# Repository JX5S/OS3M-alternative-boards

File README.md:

# OS3M-alternative-boards
Boards based on the OS3M project, using 0603s and other components I like. I tried to get as few KiCAD warning as possible.

I haven't tested the boards and I'm planning to change them further before ordering, this repository is just for reference.

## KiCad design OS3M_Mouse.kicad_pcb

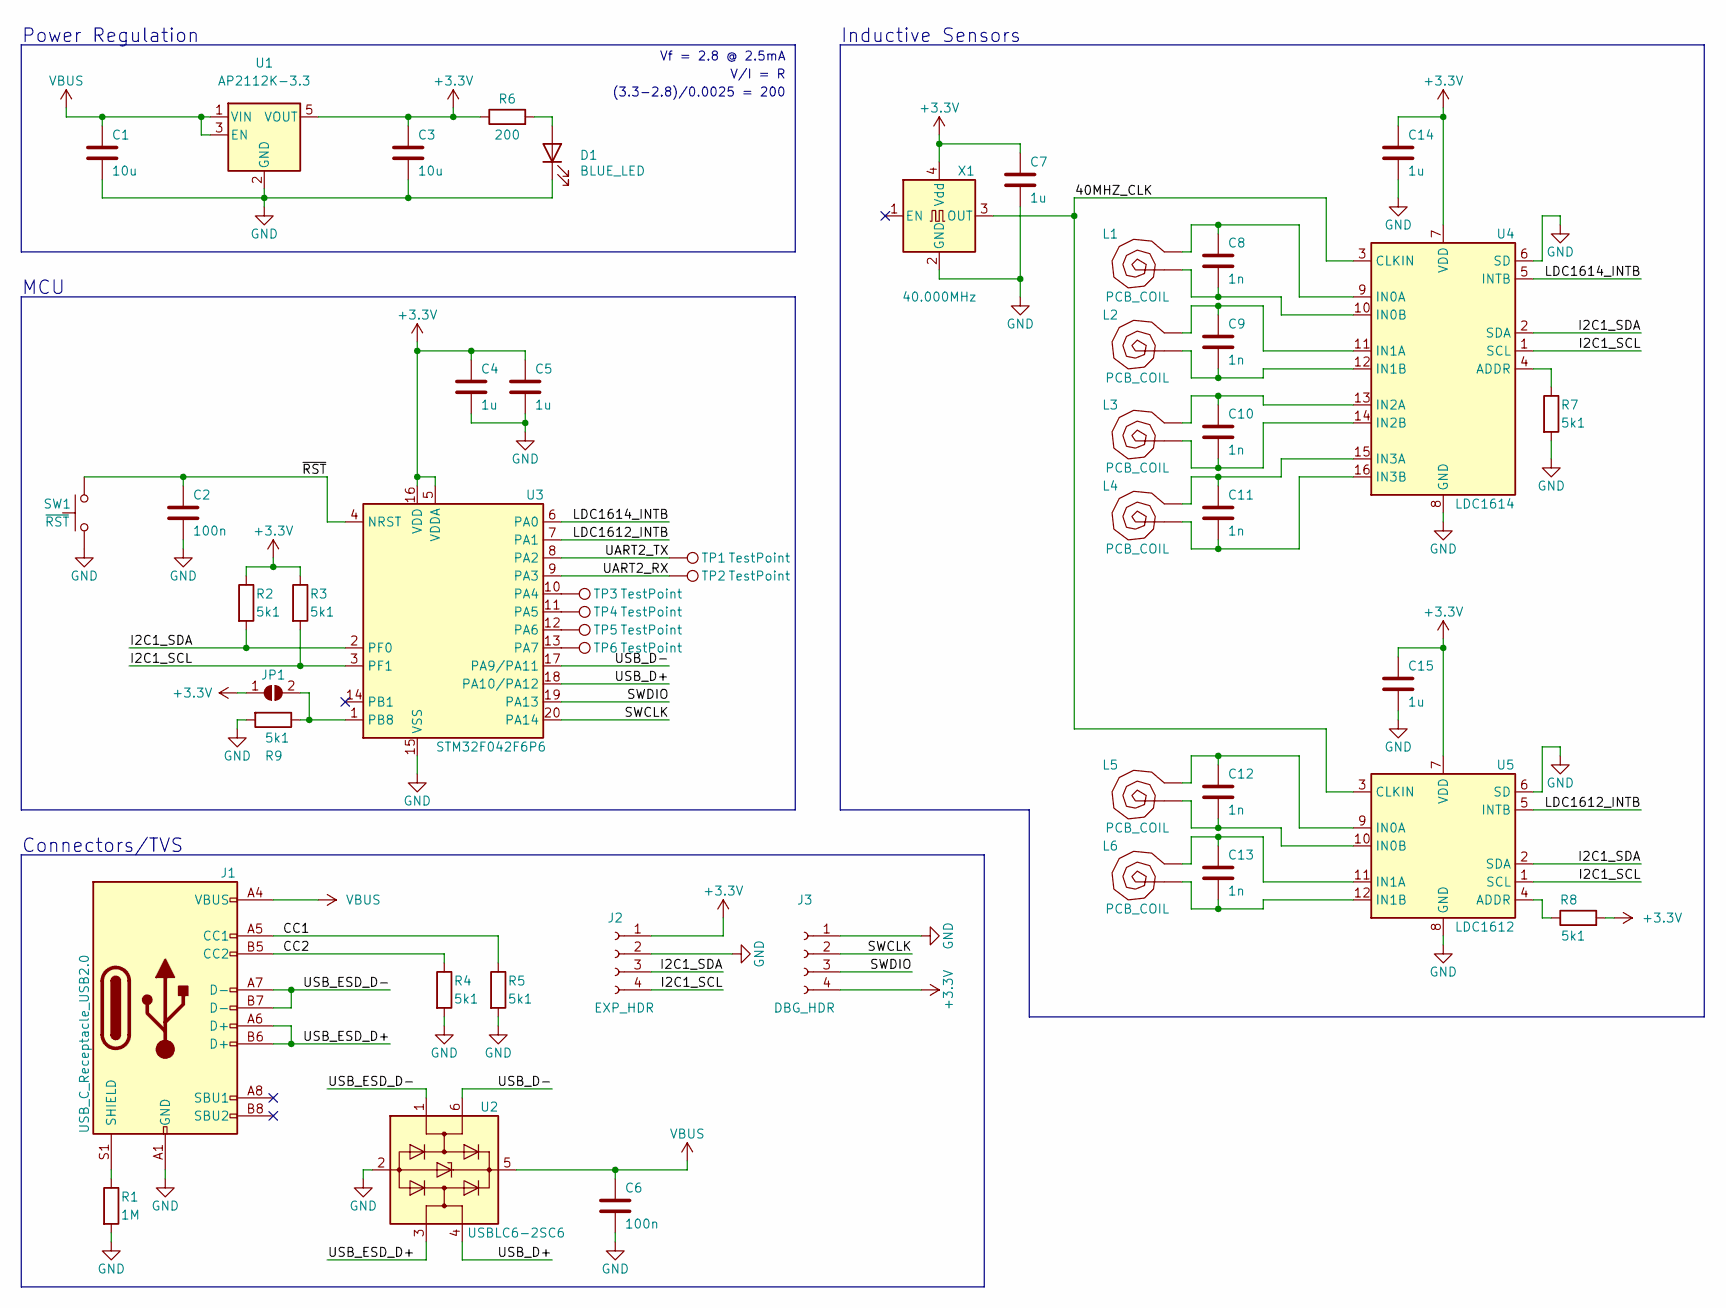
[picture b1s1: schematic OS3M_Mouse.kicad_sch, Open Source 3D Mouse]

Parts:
C1, C3: 10u; C_0603_1608Metric; LCSC C19702
C2, C6: 100n; C_0603_1608Metric; LCSC C14663
C4, C5, C7, C14, C15: 1u; C_0603_1608Metric; LCSC C15849
C8, C9, C10, C11, C12, C13: 1n; C_0603_1608Metric; LCSC C1588
D1: BLUE_LED; LED_0603_1608Metric; LCSC C72043
J1: USB_C_Receptacle_USB2.0; USB_C_Receptacle_G-Switch_GT-USB-7010ASV; LCSC C2988369
J2: EXP_HDR; PinSocket_2x02_P2.54mm_Horizontal
J3: DBG_HDR; PinHeader_1x04_P2.54mm_Vertical
JP1: SolderJumper_2_Open; SolderJumper-2_P1.3mm_Open_RoundedPad1.0x1.5mm
L1, L2, L3, L4, L5, L6: PCB_COIL; COIL_GENERATOR_0
R1: 1M; R_0603_1608Metric; LCSC C22935
R2, R3, R4, R5, R7, R8, R9: 5k1; R_0603_1608Metric; LCSC C23186
R6: 200; R_0603_1608Metric; LCSC C8218
SW1: ~{RST}; SW_Push_1P1T_XKB_TS-1187A; LCSC C318884
TP1, TP2, TP3, TP4, TP5, TP6: TestPoint; TestPoint_Pad_D2.0mm
U1: AP2112K-3.3; SOT-23-5; LCSC C51118
U2: USBLC6-2SC6; SOT-23-6; LCSC C2827654
U3: STM32F042F6P6; TSSOP-20_4.4x6.5mm_P0.65mm; LCSC C2969989
U4: LDC1614; WQFN-16-1EP_4x4mm_P0.5mm_EP2.6x2.6mm_ThermalVias; LCSC C968448
U5: LDC1612; WSON-12-1EP_4x4mm_P0.5mm_EP2.6x3mm_ThermalVias; LCSC C202191
X1: 40.000MHz; Crystal_SMD_3225-4Pin_3.2x2.5mm; LCSC C387435

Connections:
+3.3V: C3.1, C4.1, C5.1, C7.1, C14.1, C15.1, J2.1, J3.4, JP1.1 (A), R2.1, R3.1, R6.1, R8.2, U1.5 (VOUT), U3.5 (VDDA), U3.16 (VDD), U4.7 (VDD), U5.7 (VDD), X1.4 (Vdd)
/40MHZ_CLK: U4.3 (CLKIN), U5.3 (CLKIN), X1.3 (OUT)
/CC1: J1.A5 (CC1), R5.1
/CC2: J1.B5 (CC2), R4.1
/I2C1_SCL: J2.4, R3.2, U3.3 (PF1), U4.1 (SCL), U5.1 (SCL)
/I2C1_SDA: J2.3, R2.2, U3.2 (PF0), U4.2 (SDA), U5.2 (SDA)
/LDC1612_INTB: U3.7 (PA1), U5.5 (INTB)
/LDC1614_INTB: U3.6 (PA0), U4.5 (INTB)
/SWCLK: J3.2, U3.20 (PA14)
/SWDIO: J3.3, U3.19 (PA13)
/UART2_RX: TP2.1, U3.9 (PA3)
/UART2_TX: TP1.1, U3.8 (PA2)
/USB_D+: U2.4 (I/O2), U3.18 (PA10/PA12)
/USB_D-: U2.6 (I/O1), U3.17 (PA9/PA11)
/USB_ESD_D+: J1.A6 (D+), J1.B6 (D+), U2.3 (I/O2)
/USB_ESD_D-: J1.A7 (D-), J1.B7 (D-), U2.1 (I/O1)
/~RST: C2.1, SW1.2, U3.4 (NRST)
GND: C1.2, C2.2, C3.2, C4.2, C5.2, C6.2, C7.2, C14.2, C15.2, D1.1 (K), J1.A1 (GND), J1.A12 (GND), J1.B1 (GND), J1.B12 (GND), J2.2, J3.1, R1.2, R4.2, R5.2, R7.2, R9.2, SW1.1, U1.2 (GND), U2.2 (GND), U3.15 (VSS), U4.6 (SD), U4.8 (GND), U4.17 (GND), U5.6 (SD), U5.8 (GND), U5.13 (GND), X1.2 (GND)
unnamed: D1.2 (A), R6.2
unnamed: J1.S1 (SHIELD), R1.1
unnamed: JP1.2 (B), R9.1, U3.1 (PB8)
unnamed: TP3.1, U3.10 (PA4)
unnamed: TP4.1, U3.11 (PA5)
unnamed: TP5.1, U3.12 (PA6)
unnamed: TP6.1, U3.13 (PA7)
unnamed: R7.1, U4.4 (ADDR)
unnamed: C8.1, L1.1, U4.9 (IN0A)
unnamed: C8.2, L1.2, U4.10 (IN0B)
unnamed: C9.1, L2.1, U4.11 (IN1A)
unnamed: C9.2, L2.2, U4.12 (IN1B)
unnamed: C10.1, L3.1, U4.13 (IN2A)
unnamed: C10.2, L3.2, U4.14 (IN2B)
unnamed: C11.1, L4.1, U4.15 (IN3A)
unnamed: C11.2, L4.2, U4.16 (IN3B)
unnamed: R8.1, U5.4 (ADDR)
unnamed: C12.1, L5.1, U5.9 (IN0A)
unnamed: C12.2, L5.2, U5.10 (IN0B)
unnamed: C13.1, L6.1, U5.11 (IN1A)
unnamed: C13.2, L6.2, U5.12 (IN1B)
VBUS: C1.1, C6.1, J1.A4 (VBUS), J1.A9 (VBUS), J1.B4 (VBUS), J1.B9 (VBUS), U1.1 (VIN), U1.3 (EN), U2.5 (VBUS)

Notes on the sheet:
Inductive Sensors
MCU
Power Regulation
(3.3-2.8)/0.0025 = 200
V/I = R
Connectors/TVS
Vf = 2.8 @ 2.5mA

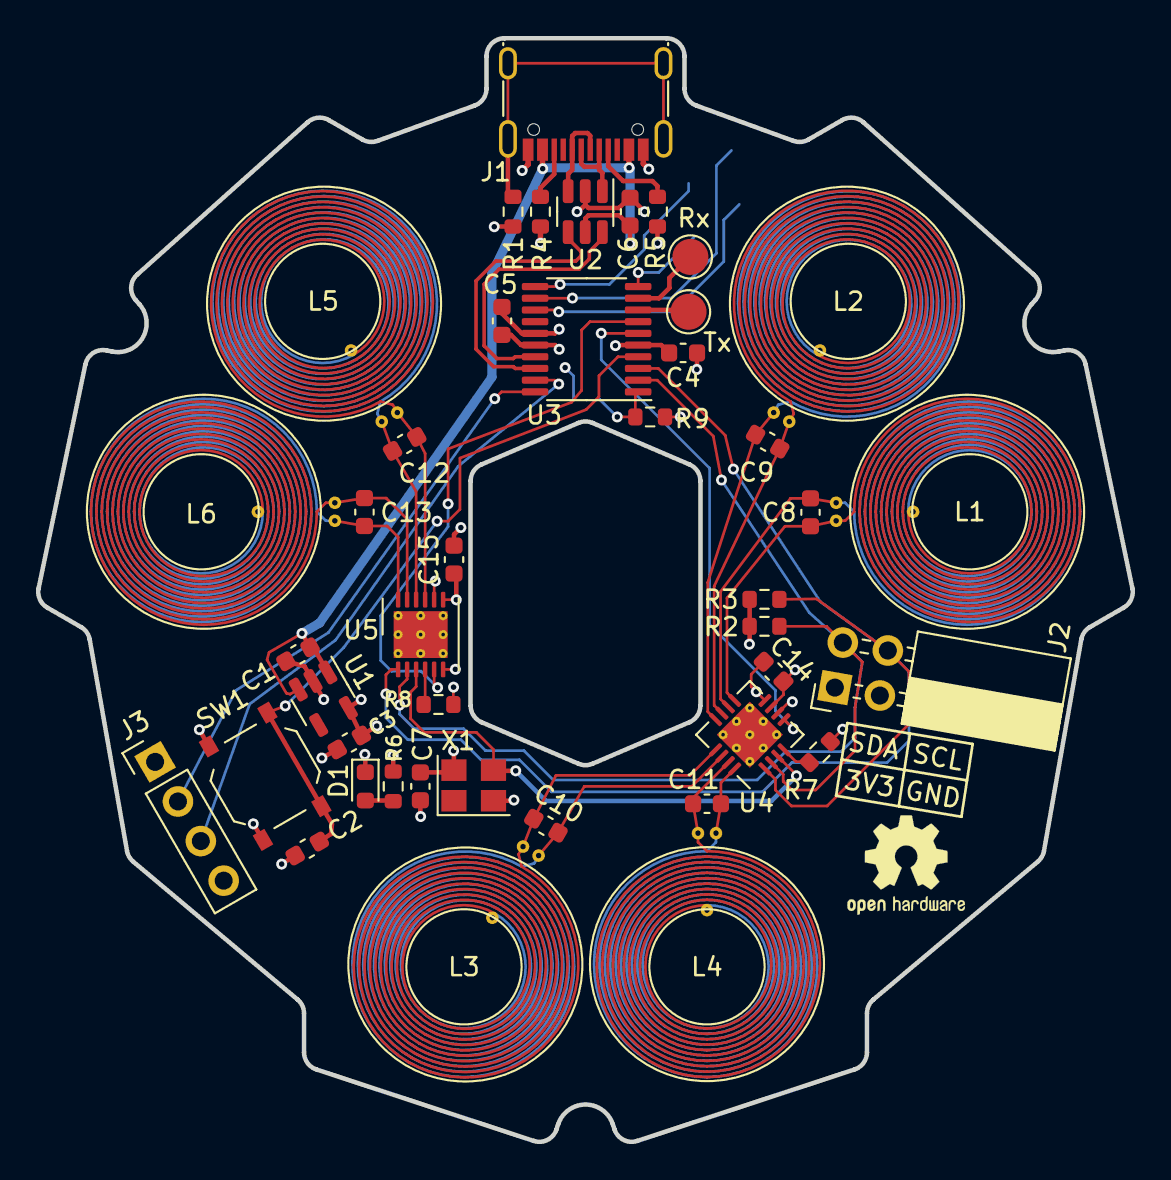
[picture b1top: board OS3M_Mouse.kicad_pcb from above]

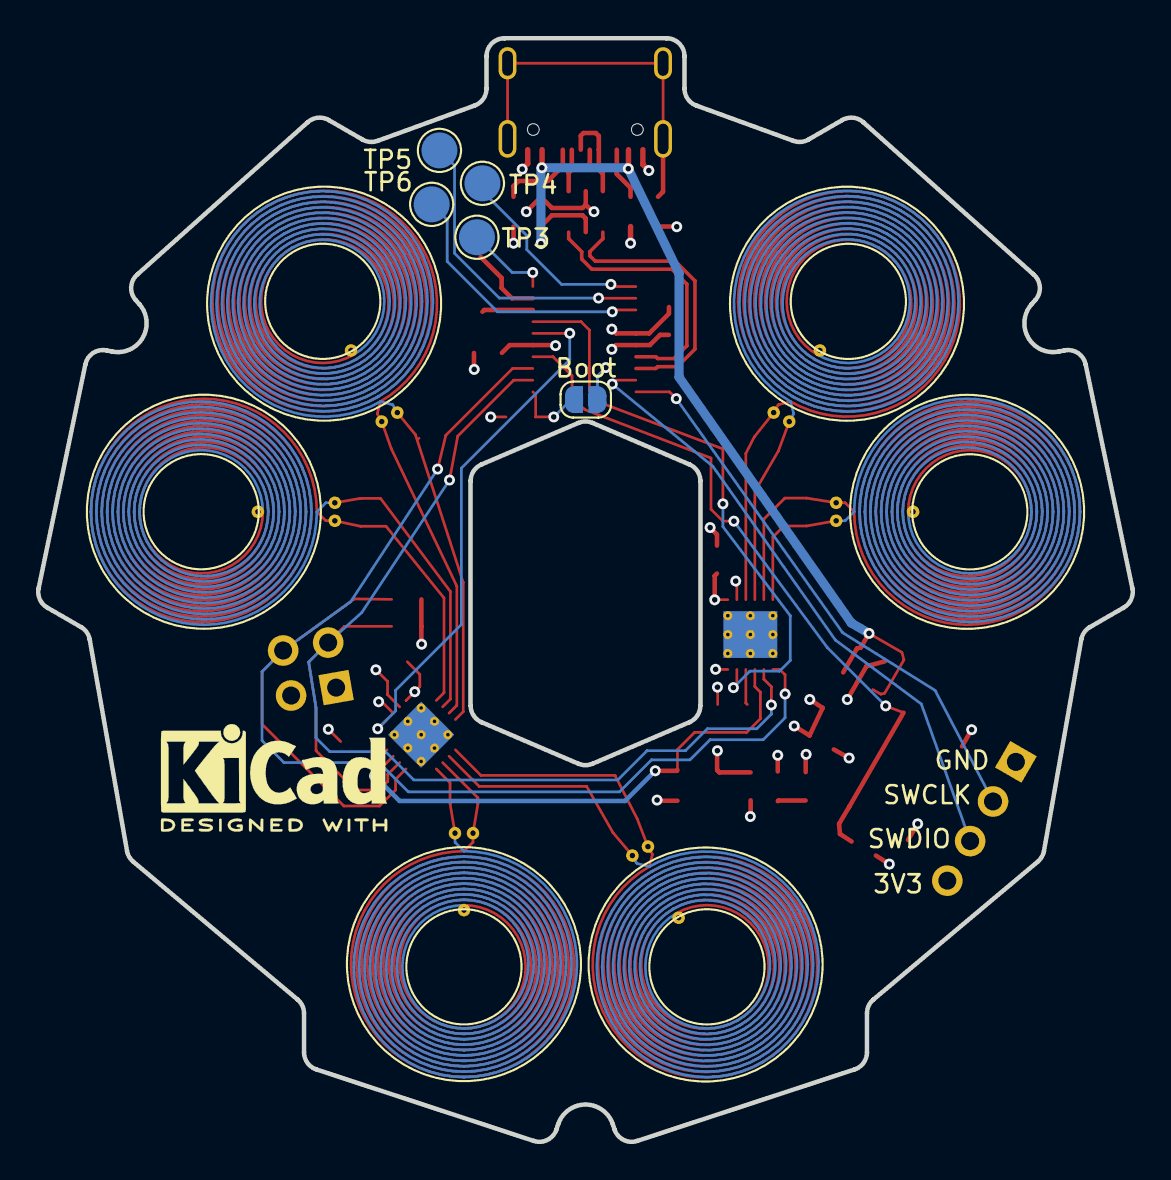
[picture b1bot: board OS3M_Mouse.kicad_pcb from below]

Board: 4 copper layers, 60.8 x 61.3 mm, 48 parts (5 on the bottom side), 40 nets.
